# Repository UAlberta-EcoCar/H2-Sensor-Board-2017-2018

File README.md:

# H2-Sensor-(Safety)-Board
Repository for the hydrogen sensor (safety) board and associated code.

This board is responsible for shutting down the FCC system in case of a H2 leak, E-stop button push or remote-kill signal.

Preliminary documentation (to be moved to Wiki): https://drive.google.com/open?id=1S8betwiyb474213RZoNG3XHaL3DfAaQFg7lT7IdTJPk

Folder on Google Drive with other related files: https://drive.google.com/open?id=1GxiV1qDfL8EswHq86x-2SQPqP8KY5xJN

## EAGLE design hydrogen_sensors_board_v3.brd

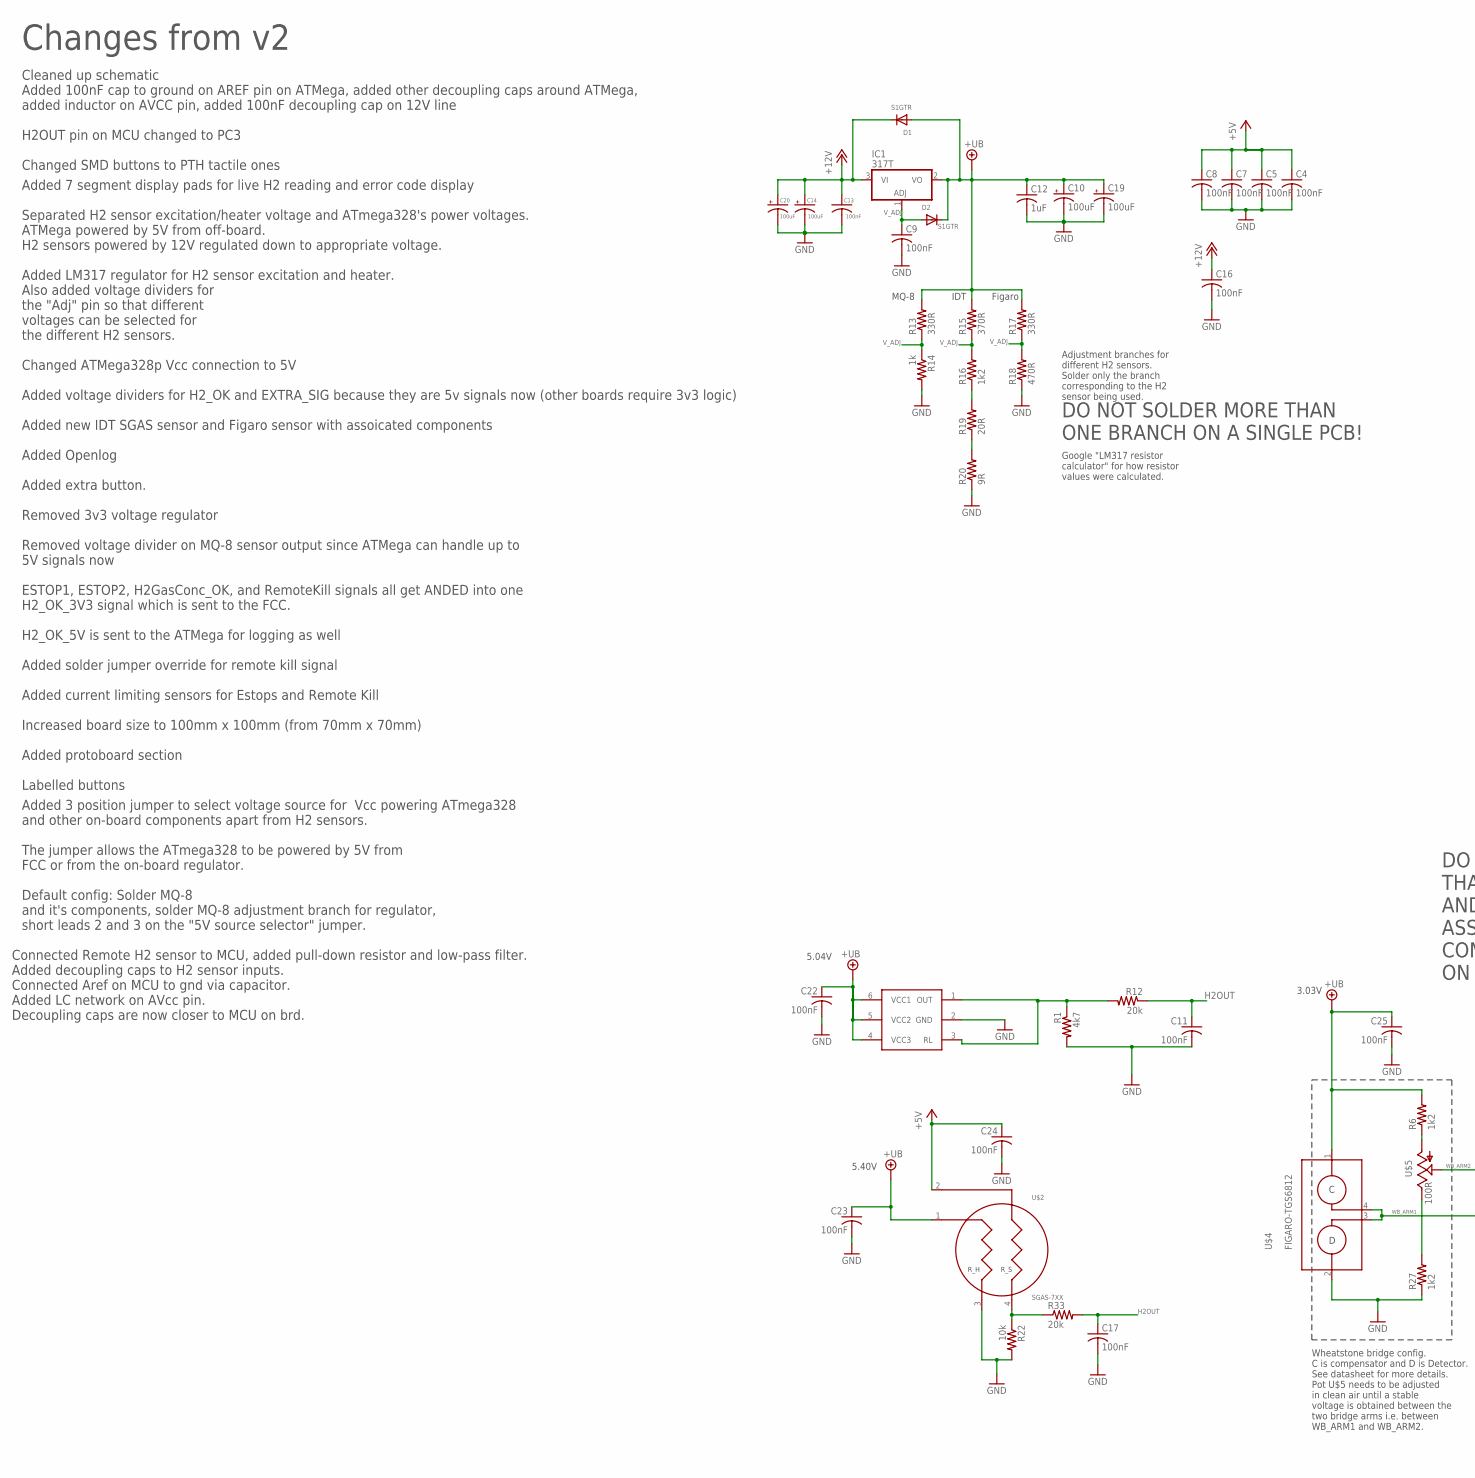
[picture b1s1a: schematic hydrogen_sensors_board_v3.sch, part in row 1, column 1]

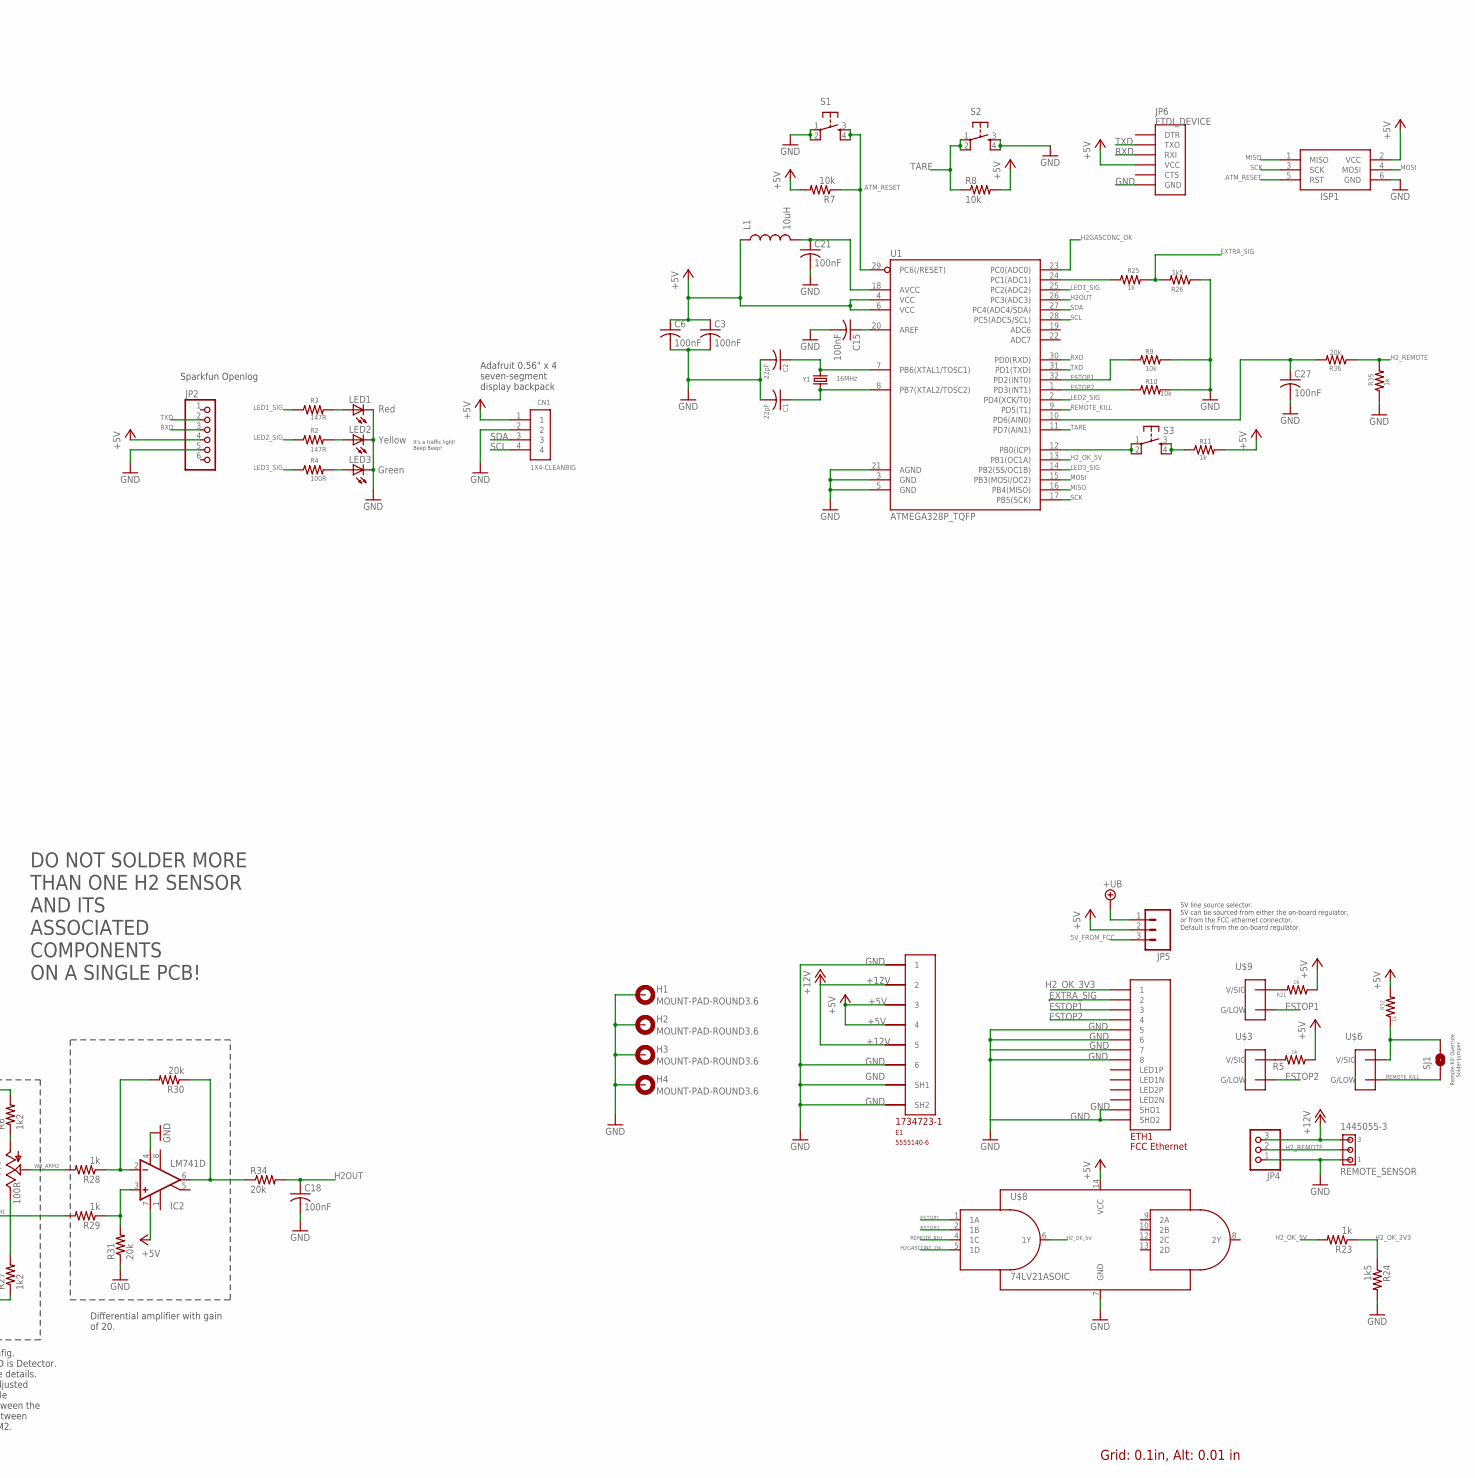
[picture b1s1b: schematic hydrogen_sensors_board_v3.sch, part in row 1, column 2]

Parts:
C1, C2: 22pF; C0603K
C3, C4, C5, C6, C7, C8, C9, C11, C13, C15, C16, C17, C18, C21, C22, C23, C24, C25, C27: 100nF; C0603
C10, C14: 100uF; B/3528-21R
C12: 1uF; C0603
C19, C20: 100uF; CPOL-RADIAL-100UF-25V
CN1: 1X4-CLEANBIG; 1X04-CLEANBIG
D1, D2: S1GTR; SMADIODE
E1: 5555140-6; 1734723-1_RJ11
ETH1: FCC Ethernet; A122645-ND
H1, H2, H3, H4: MOUNT-PAD-ROUND3.6; 3,6-PAD
IC1: 317T; TO220H
IC2: LM741D; SO08
ISP1: AVRISP-BOX
JP2: PINHD-1X6LOCK; 1X06-BIGLOCK
JP4: PINHD-1X3; 1X03
JP5: M03PTH; 1X03
JP6: FTDI_DEVICE; FTDI_DEVICE_SIDE
L1: 10uH; 0603
LED1: Red; CHIPLED_0805
LED2: Yellow; CHIPLED_0805
LED3: Green; CHIPLED_0805
R1: 4k7; 0603-RES
R2, R3: 147R; 0603-RES
R4: 100R; 0603-RES
R5, R11, R14, R21, R23, R25, R28, R29, R32, R35: 1k; 0603-RES
R6, R16, R27: 1k2; 0603-RES
R7, R8, R9, R10, R22: 10k; 0603-RES
R12, R30, R31, R33, R34, R36: 20k; 0603-RES
R13, R17: 330R; 0603-RES
R15: 370R; 0603-RES
R18: 470R; 0603-RES
R19: 20R; 0603-RES
R20: 9R; 0603-RES
R24, R26: 1k5; 0603-RES
REMOTE_SENSOR: 1445055-3
S1, S2, S3: TAC_SWITCHPTH; TACTILE-PTH
SJ1: SOLDERJUMPERNO; SJ_2S-NO
U1: ATMEGA328P_TQFP; TQFP32-08
U$1: MQ-8MQ-8; MQ-8
U$2: SGAS-7XX; TO39
U$3, U$6, U$9: TE770966; 2X1-MATE-N-LOCK
U$4: FIGARO-TGS6812; 4PTH
U$5: 100R; 3362U
U$8: 74LV21ASOIC; SOIC-14
Y1: 16MHz; HC49US

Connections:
5V_FROM_FCC: JP5.3
+5V: C3.1, C4.1, C5.1, C6.1, C7.1, C8.1, C24.1, CN1.1, E1.3, E1.4, IC2.7 (V+), ISP1.2 (VCC), JP2.4, JP5.2, JP6.P$4 (VCC), L1.1, R5.1, R7.2, R8.2, R11.2, R21.1, R32.2, U1.4 (VCC), U1.6 (VCC), U$2.2, U$8.14 (VCC)
+12V: C13.1, C14.+, C16.1, C20.1 (+), D1.C, E1.2, E1.5, IC1.3 (VI), JP4.3, REMOTE_SENSOR.3
+UB: C10.+, C12.1, C19.1 (+), C22.1, C23.1, C25.1, D1.A, D2.C, IC1.2 (VO), JP5.1, R6.2, R13.2, R15.2, R17.2, U$1.4 (VCC3), U$1.5 (VCC2), U$1.6 (VCC1), U$2.1, U$4.1
ATM_RESET: ISP1.5 (RST), R7.1, S1.3, S1.4, U1.29 (PC6(/RESET))
ESTOP1: ETH1.P$3 (3), R9.1, U1.32 (PD2(INT0)), U$8.1 (1A), U$9.CIRCUIT2 (G/LOW)
ESTOP2: ETH1.P$4 (4), R10.1, U1.1 (PD3(INT1)), U$3.CIRCUIT2 (G/LOW), U$8.2 (1B)
EXTRA_SIG: ETH1.P$2 (2), R25.2, R26.2
GND: C1.2, C2.2, C3.2, C4.2, C5.2, C6.2, C7.2, C8.2, C9.2, C10.-, C11.2, C12.2, C13.2, C14.-, C15.2, C16.2, C17.2, C18.2, C19.2 (-), C20.2 (-), C21.2, C22.2, C23.2, C24.2, C25.2, C27.2, CN1.2, E1.1, E1.6, E1.SH1, E1.SH2, ETH1.P$5 (5), ETH1.P$6 (6), ETH1.P$7 (7), ETH1.P$8 (8), ETH1.P$13 (SHD1), ETH1.P$14 (SHD2), H1.B3,6, H2.B3,6, H3.B3,6, H4.B3,6, IC2.4 (V-), ISP1.6 (GND), JP2.5, JP4.1, JP6.P$6 (GND), LED1.C, LED2.C, LED3.C, R1.2, R9.2, R10.2, R14.2, R18.1, R20.1, R22.2, R24.2, R26.1, R27.1, R31.1, R35.1, REMOTE_SENSOR.1, S1.1, S1.2, S2.3, S2.4, U1.3 (GND), U1.5 (GND), U1.21 (AGND), U$1.2 (GND), U$2.3, U$4.2, U$8.7 (GND)
H2GASCONC_OK: U1.23 (PC0(ADC0)), U$8.5 (1D)
H2OUT: C11.1, C17.1, C18.1, R12.1, R33.2, R34.2, U1.26 (PC3(ADC3))
H2_OK_3V3: ETH1.P$1 (1), R23.1, R24.1
H2_OK_5V: R23.2, U1.13 (PB1(OC1A)), U$8.6 (1Y)
H2_REMOTE: JP4.2, R35.2, R36.1, REMOTE_SENSOR.2
LED1_SIG: R3.1, U1.25 (PC2(ADC2))
LED2_SIG: R2.1, U1.2 (PD4(XCK/T0))
LED3_SIG: R4.1, U1.14 (PB2(SS/OC1B))
MISO: ISP1.1 (MISO), U1.16 (PB4(MISO))
MOSI: ISP1.4 (MOSI), U1.15 (PB3(MOSI/OC2))
unnamed: C2.1, U1.7 (PB6(XTAL1/TOSC1)), Y1.2
unnamed: R6.1, U$5.P$3 (A)
unnamed: C1.1, U1.8 (PB7(XTAL2/TOSC2)), Y1.1
unnamed: C15.1, U1.20 (AREF)
unnamed: R22.1, R33.1, U$2.4
unnamed: C27.1, R36.2, U1.10 (PD6(AIN0))
unnamed: LED1.A, R3.2
unnamed: LED2.A, R2.2
unnamed: LED3.A, R4.2
unnamed: R27.2, U$5.P$1 (E)
unnamed: R21.2, U$9.CIRCUIT1 (V/SIG)
unnamed: R25.1, U1.24 (PC1(ADC1))
unnamed: IC2.2 (-IN), R28.1, R30.2
unnamed: R16.1, R19.2
unnamed: S3.1, S3.2, U1.12 (PB0(ICP))
unnamed: R11.1, S3.3, S3.4
unnamed: R19.1, R20.2
unnamed: R1.1, R12.2, U$1.1 (OUT), U$1.3 (RL)
unnamed: IC2.6 (OUT), R30.1, R34.1
unnamed: R5.2, U$3.CIRCUIT1 (V/SIG)
unnamed: IC2.3 (+IN), R29.1, R31.2
unnamed: R32.1, SJ1.2, U$6.CIRCUIT1 (V/SIG)
unnamed: C21.1, L1.2, U1.18 (AVCC)
REMOTE_KILL: SJ1.1, U1.9 (PD5(T1)), U$6.CIRCUIT2 (G/LOW), U$8.4 (1C)
RXD: JP2.3, JP6.P$3 (RXI), U1.30 (PD0(RXD))
SCK: ISP1.3 (SCK), U1.17 (PB5(SCK))
SCL: CN1.4, U1.28 (PC5(ADC5/SCL))
SDA: CN1.3, U1.27 (PC4(ADC4/SDA))
TARE: R8.1, S2.1, S2.2, U1.11 (PD7(AIN1))
TXD: JP2.2, JP6.P$2 (TXO), U1.31 (PD1(TXD))
V_ADJ: C9.1, D2.A, IC1.1 (ADJ), R13.1, R14.1, R15.1, R16.2, R17.1, R18.2
WB_ARM1: R29.2, U$4.3, U$4.4
WB_ARM2: R28.2, U$5.P$2 (S)

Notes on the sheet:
Changes from v2
H2OUT pin on MCU changed to PC3
Changed SMD buttons to PTH tactile ones
Added 7 segment display pads for live H2 reading and error code display
Added LM317 regulator for H2 sensor excitation and heater. Also added voltage dividers for the "Adj" pin so that different voltages can be selected for the different H2 sensors.
Adafruit 0.56" x 4 seven-segment display backpack
Sparkfun Openlog
IDT
MQ-8
Figaro
Changed ATMega328p Vcc connection to 5V
Added voltage dividers for H2_OK and EXTRA_SIG because they are 5v signals now (other boards require 3v3 logic)
Added new IDT SGAS sensor and Figaro sensor with assoicated components
Added Openlog
Added extra button.
Removed 3v3 voltage regulator
Wheatstone bridge config. C is compensator and D is Detector. See datasheet for more details. Pot U$5 needs to be adjusted in clean air until a stable voltage is obtained between the two bridge arms i.e. between WB_ARM1 and WB_ARM2.
Differential amplifier with gain of 20.
3.03V
5.40V
5.04V
Adjustment branches for different H2 sensors. Solder only the branch corresponding to the H2 sensor being used.
DO NOT SOLDER MORE THAN ONE H2 SENSOR AND ITS ASSOCIATED COMPONENTS ON A SINGLE PCB!
It's a traffic light! Beep Beep!
Google "LM317 resistor calculator" for how resistor values were calculated.
Removed voltage divider on MQ-8 sensor output since ATMega can handle up to 5V signals now ESTOP1, ESTOP2, H2GasConc_OK, and RemoteKill signals all get ANDED into one H2_OK_3V3 signal which is sent to the FCC.
Grid: 0.1in, Alt: 0.01 in
Cleaned up schematic Added 100nF cap to ground on AREF pin on ATMega, added other decoupling caps around ATMega, added inductor on AVCC pin, added 100nF decoupling cap on 12V line
Increased board size to 100mm x 100mm (from 70mm x 70mm) Added protoboard section Labelled buttons
Separated H2 sensor excitation/heater voltage and ATmega328's power voltages. ATMega powered by 5V from off-board. H2 sensors powered by 12V regulated down to appropriate voltage.
DO NOT SOLDER MORE THAN ONE BRANCH ON A SINGLE PCB!
H2_OK_5V is sent to the ATMega for logging as well
Added solder jumper override for remote kill signal Added current limiting sensors for Estops and Remote Kill
Added 3 position jumper to select voltage source for Vcc powering ATmega328 and other on-board components apart from H2 sensors. The jumper allows the ATmega328 to be powered by 5V from FCC or from the on-board regulator. Default config: Solder MQ-8 and it's components, solder MQ-8 adjustment branc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
Remote Kill Override Solder Jumper
5V line source selector. 5V can be sourced from either the on-board regulator, or from the FCC ethernet connector. Default is from the on-board regulator.
Connected Remote H2 sensor to MCU, added pull-down resistor and low-pass filter. Added decoupling caps to H2 sensor inputs. Connected Aref on MCU to gnd via capacitor. Added LC network on AVcc pin. Decoupling caps are now closer to MCU on brd.

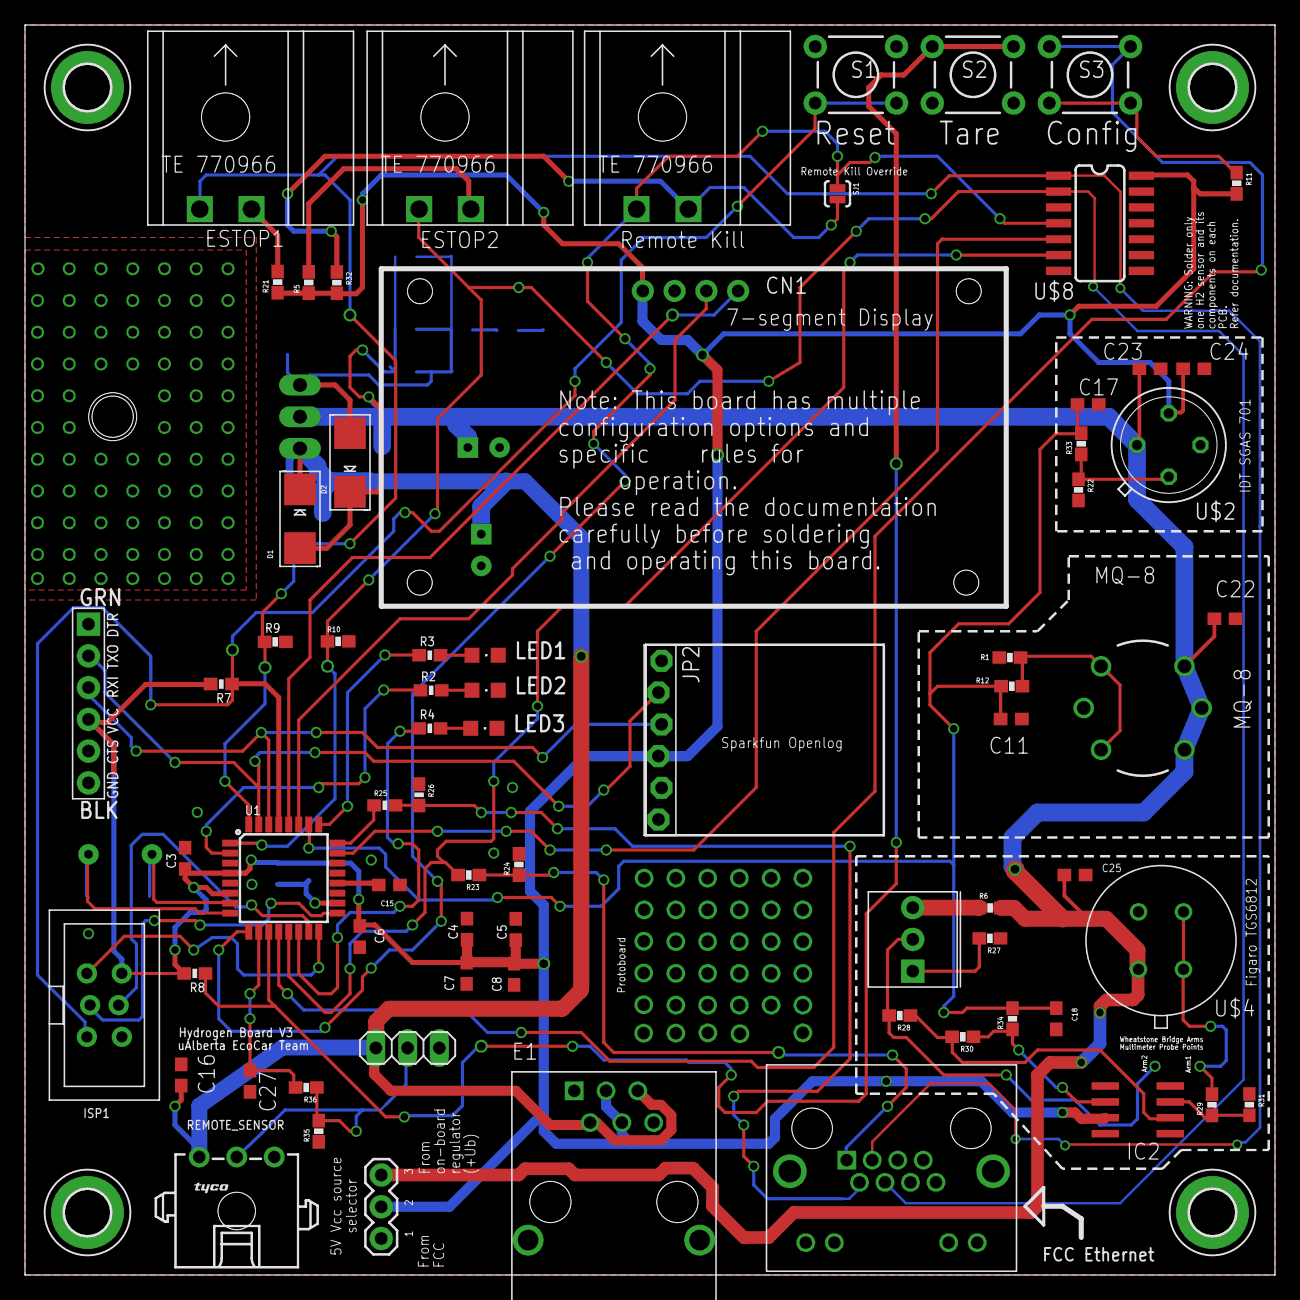
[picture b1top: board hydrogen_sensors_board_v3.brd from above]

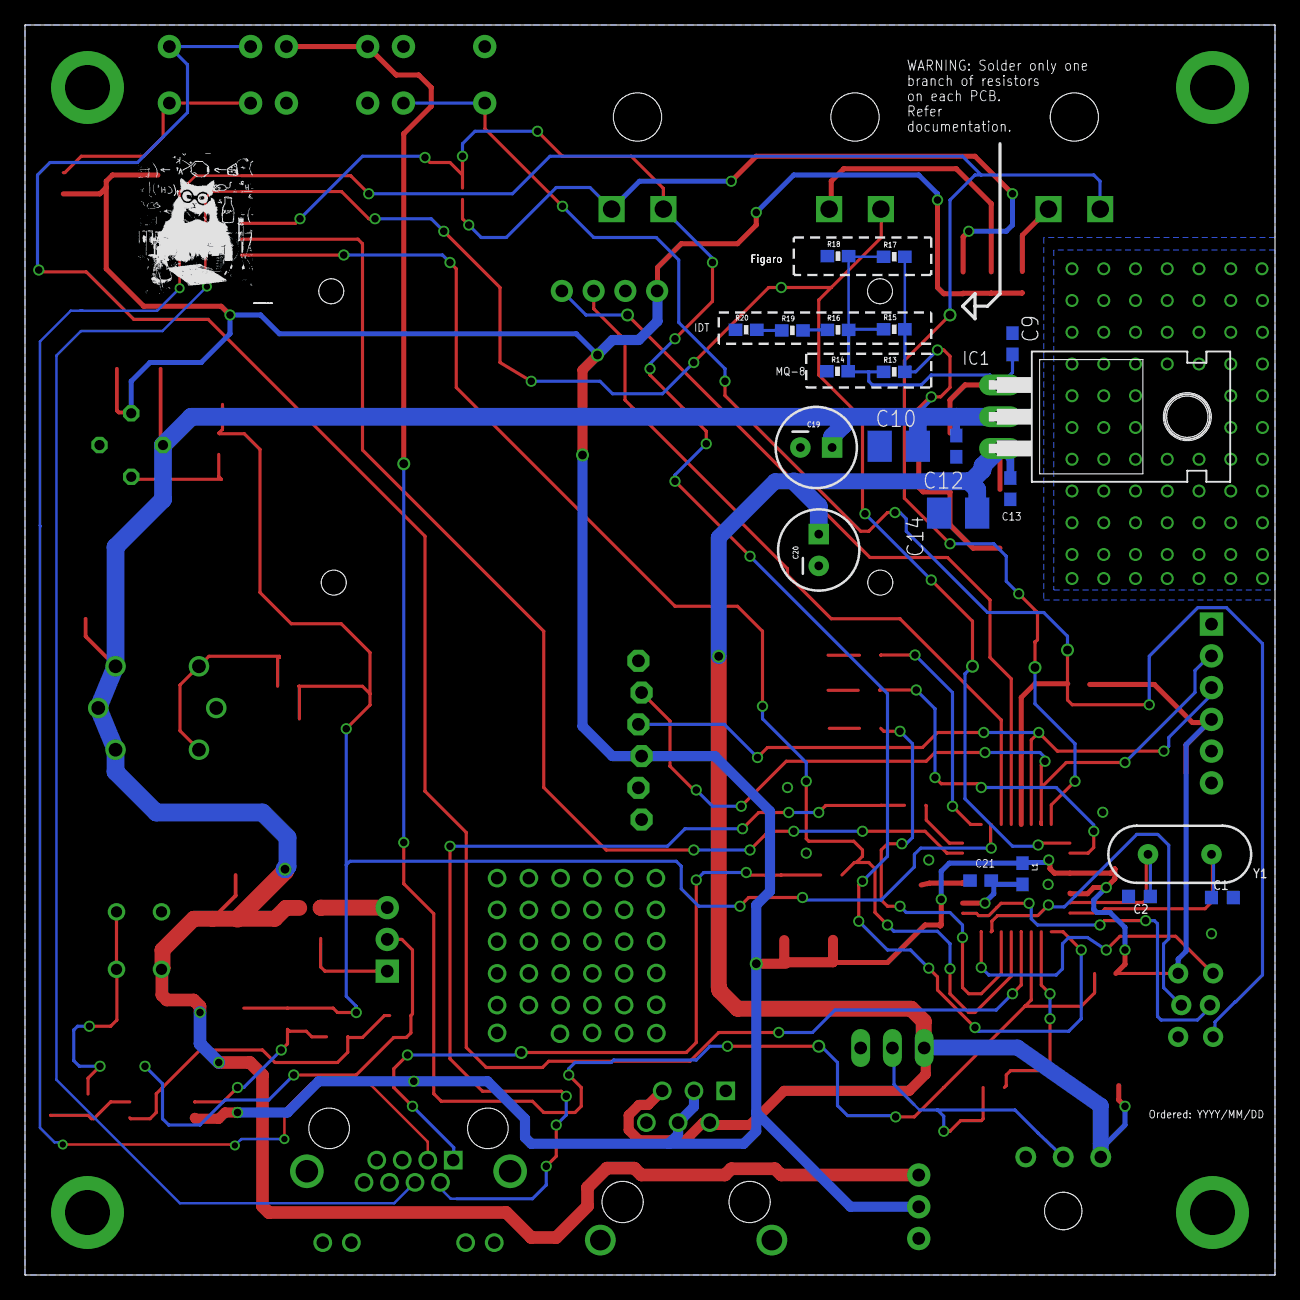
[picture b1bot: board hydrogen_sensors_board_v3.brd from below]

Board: 2 copper layers, 100.0 x 100.0 mm, 97 parts (21 on the bottom side), 51 nets.

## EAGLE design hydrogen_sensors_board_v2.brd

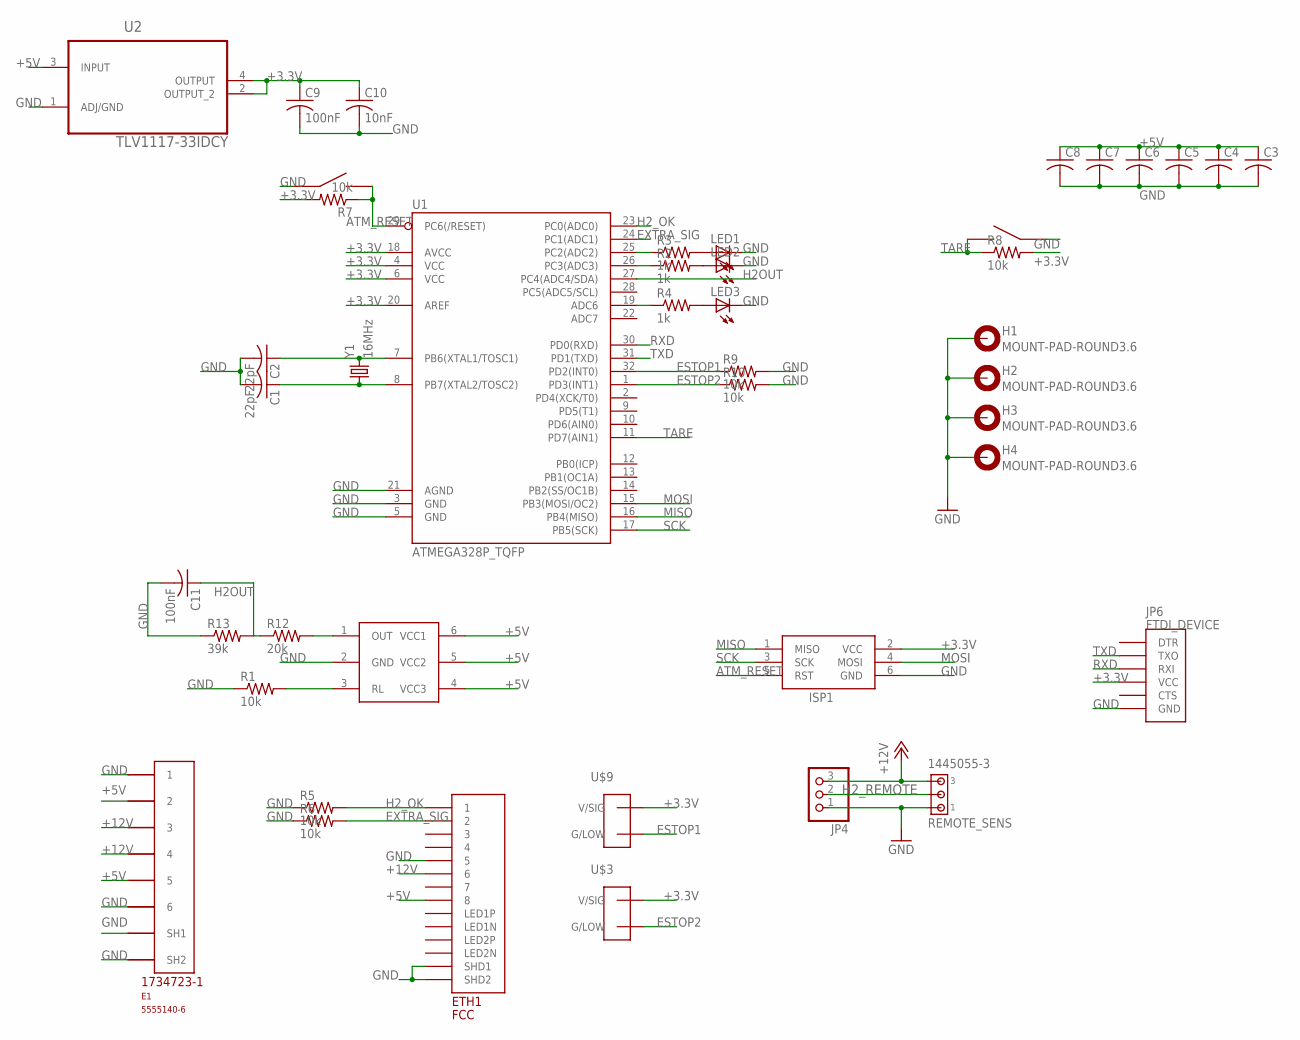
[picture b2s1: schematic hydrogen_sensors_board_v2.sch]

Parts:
C1, C2: 22pF; C0603K
C3, C4, C5, C6, C7, C8: C-USC0603; C0603
C9, C11: 100nF; C0603
C10: 10nF; C0603
E1: 5555140-6; 1734723-1_RJ11
ETH1: FCC; A122645-ND
H1, H2, H3, H4: MOUNT-PAD-ROUND3.6; 3,6-PAD
ISP1: AVRISP-BOX
JP4: PINHD-1X3; 1X03
JP6: FTDI_DEVICE; FTDI_DEVICE_SIDE
LED1, LED2, LED3: LEDCHIPLED_0805; CHIPLED_0805
R1, R5, R6, R7, R8, R9, R10: 10k; 0603-RES
R2, R3, R4: 1k; 0603-RES
R12: 20k; 0603-RES
R13: 39k; 0603-RES
REMOTE_SENS: 1445055-3
U1: ATMEGA328P_TQFP; TQFP32-08
U2: TLV1117-33IDCY; SOT230P700X180-4N
U$1: MQ-8MQ-8; MQ-8
U$2, U$10: EG4621CT-ND
U$3, U$9: TE770966; 2X1-MATE-N-LOCK
Y1: 16MHz; HC49US

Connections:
+3.3V: C9.1, C10.1, ISP1.2 (VCC), JP6.P$4 (VCC), R7.2, R8.2, U1.4 (VCC), U1.6 (VCC), U1.18 (AVCC), U1.20 (AREF), U2.2 (OUTPUT_2), U2.4 (OUTPUT), U$3.CIRCUIT1 (V/SIG), U$9.CIRCUIT1 (V/SIG)
+5V: C3.1, C4.1, C5.1, C6.1, C7.1, C8.1, E1.2, E1.5, ETH1.P$8 (8), U2.3 (INPUT), U$1.4 (VCC3), U$1.5 (VCC2), U$1.6 (VCC1)
+12V: E1.3, E1.4, ETH1.P$6 (6), JP4.3, REMOTE_SENS.3
ATM_RESET: ISP1.5 (RST), R7.1, U1.29 (PC6(/RESET)), U$10.P$3, U$10.P$4
ESTOP1: R9.1, U1.32 (PD2(INT0)), U$9.CIRCUIT2 (G/LOW)
ESTOP2: R10.1, U1.1 (PD3(INT1)), U$3.CIRCUIT2 (G/LOW)
EXTRA_SIG: ETH1.P$2 (2), R6.2, U1.24 (PC1(ADC1))
GND: C1.2, C2.2, C3.2, C4.2, C5.2, C6.2, C7.2, C8.2, C9.2, C10.2, C11.2, E1.1, E1.6, E1.SH1, E1.SH2, ETH1.P$5 (5), ETH1.P$13 (SHD1), ETH1.P$14 (SHD2), H1.B3,6, H2.B3,6, H3.B3,6, H4.B3,6, ISP1.6 (GND), JP4.1, JP6.P$6 (GND), LED1.C, LED2.C, LED3.C, R1.1, R5.1, R6.1, R9.2, R10.2, R13.1, REMOTE_SENS.1, U1.3 (GND), U1.5 (GND), U1.21 (AGND), U2.1 (ADJ/GND), U$1.2 (GND), U$2.P$1, U$2.P$2, U$10.P$1, U$10.P$2
H2OUT: C11.1, R12.1, R13.2, U1.27 (PC4(ADC4/SDA))
H2_OK: ETH1.P$1 (1), R5.2, U1.23 (PC0(ADC0))
H2_REMOTE: JP4.2, REMOTE_SENS.2
MISO: ISP1.1 (MISO), U1.16 (PB4(MISO))
MOSI: ISP1.4 (MOSI), U1.15 (PB3(MOSI/OC2))
unnamed: C2.1, U1.7 (PB6(XTAL1/TOSC1)), Y1.2
unnamed: R1.2, U$1.3 (RL)
unnamed: C1.1, U1.8 (PB7(XTAL2/TOSC2)), Y1.1
unnamed: R3.1, U1.25 (PC2(ADC2))
unnamed: R2.1, U1.26 (PC3(ADC3))
unnamed: R4.1, U1.19 (ADC6)
unnamed: LED1.A, R3.2
unnamed: LED2.A, R2.2
unnamed: LED3.A, R4.2
unnamed: R12.2, U$1.1 (OUT)
RXD: JP6.P$3 (RXI), U1.30 (PD0(RXD))
SCK: ISP1.3 (SCK), U1.17 (PB5(SCK))
TARE: R8.1, U1.11 (PD7(AIN1)), U$2.P$3, U$2.P$4
TXD: JP6.P$2 (TXO), U1.31 (PD1(TXD))

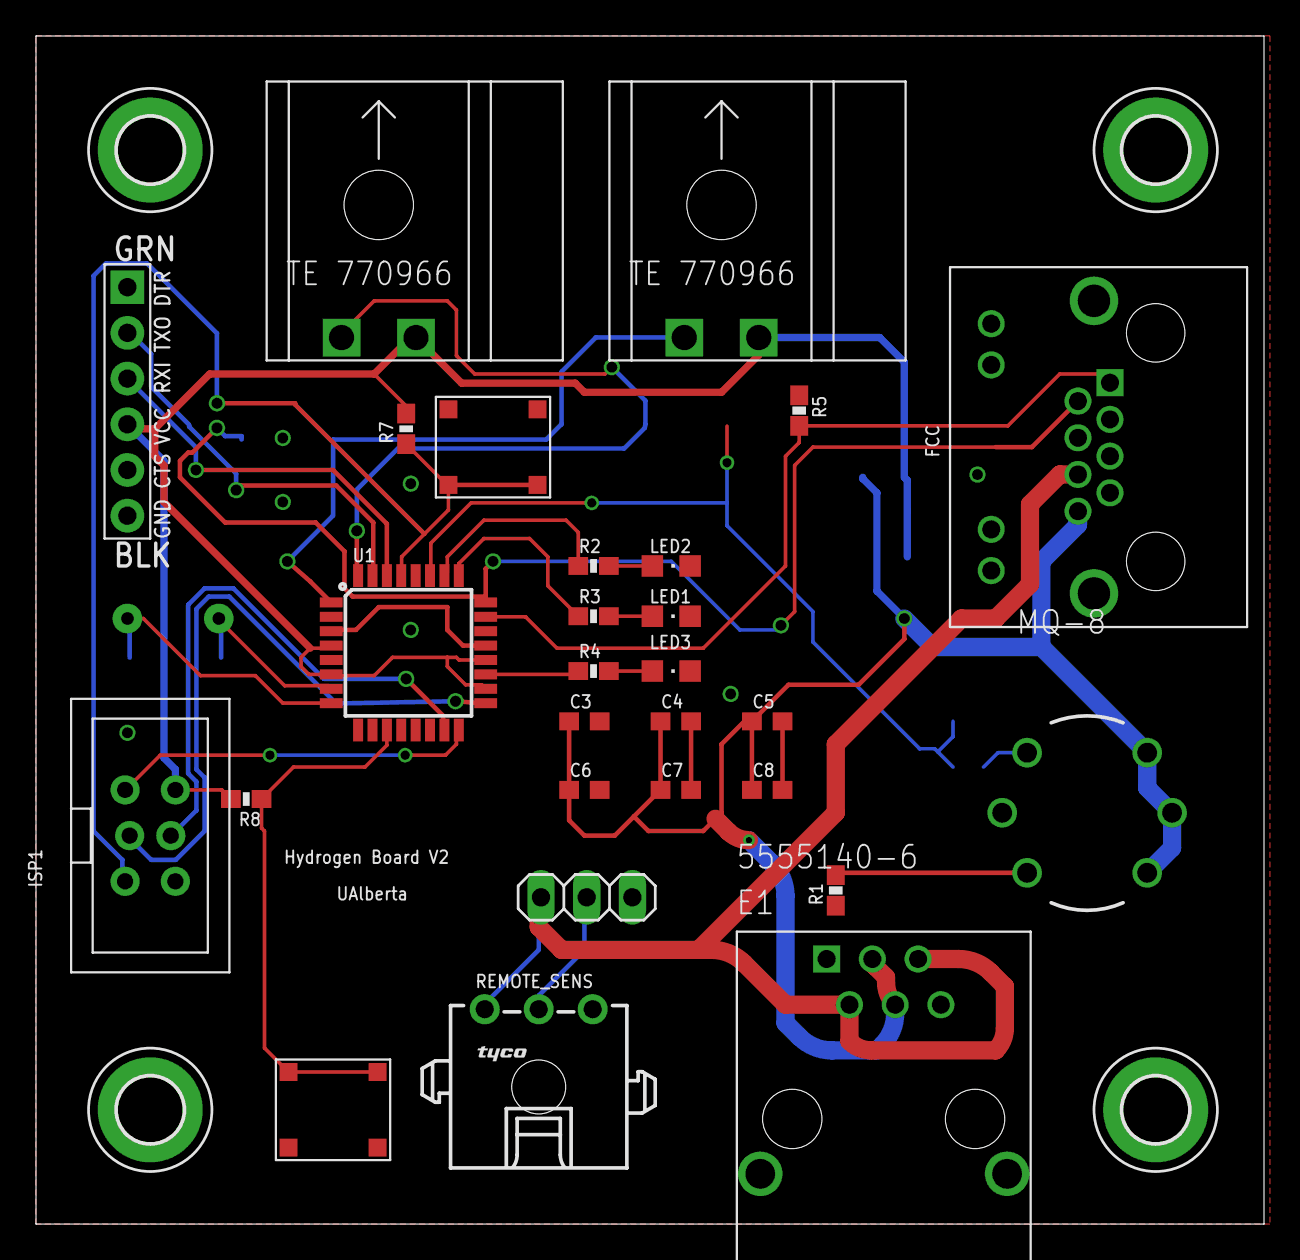
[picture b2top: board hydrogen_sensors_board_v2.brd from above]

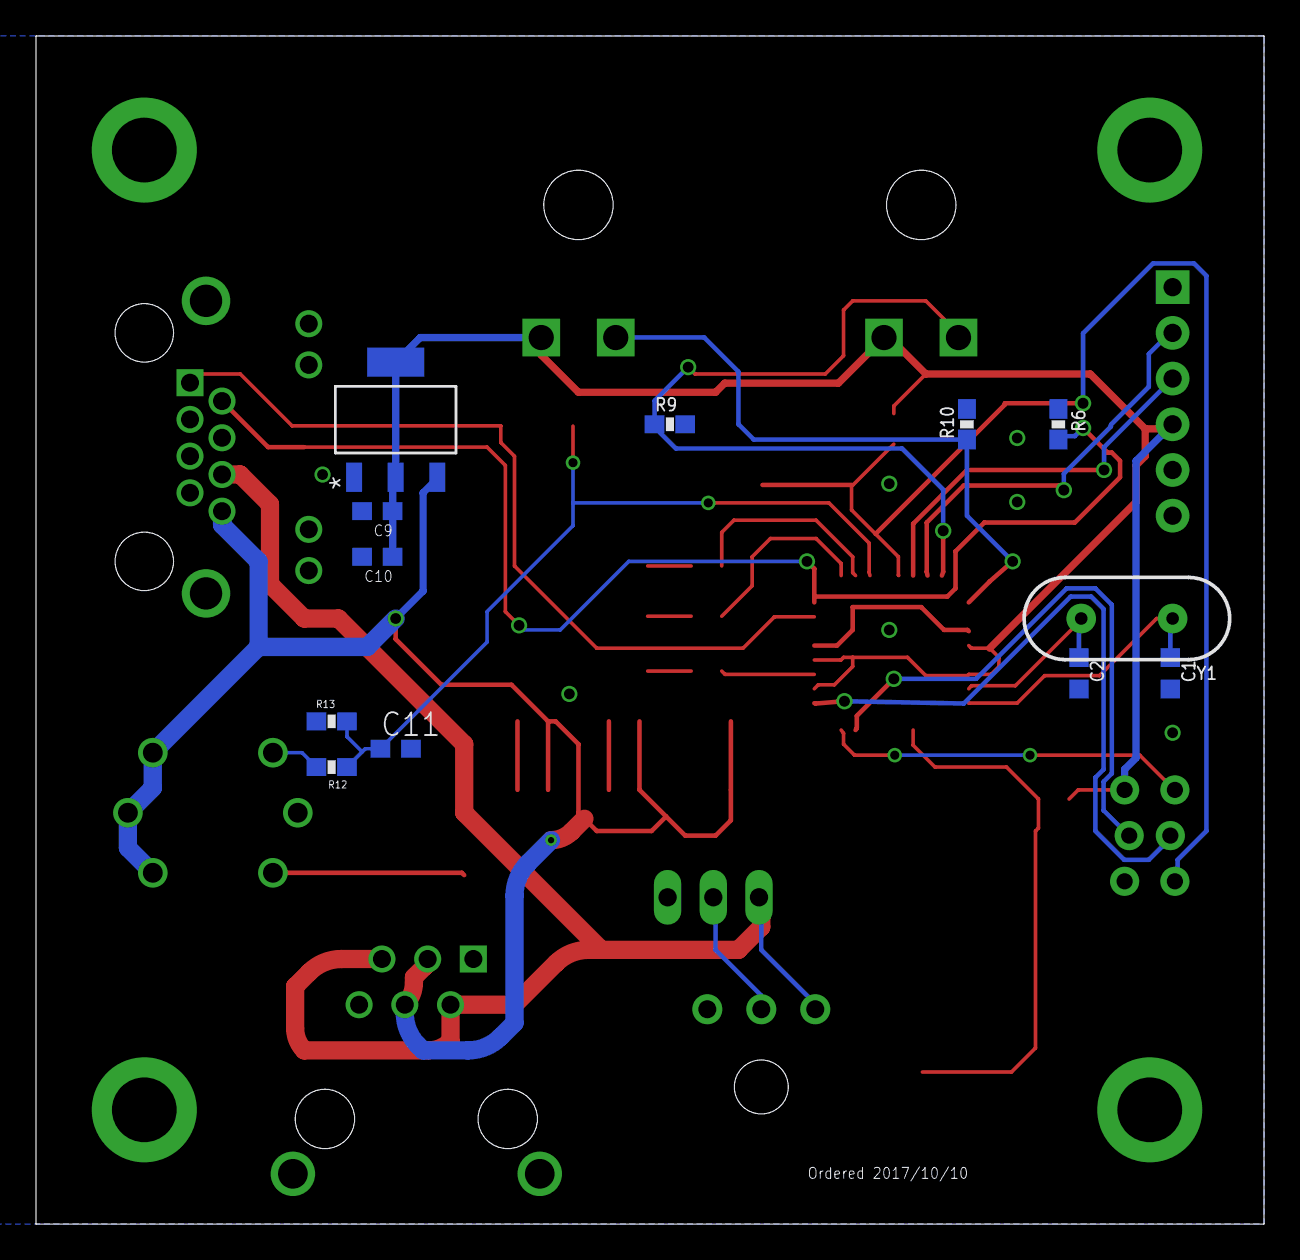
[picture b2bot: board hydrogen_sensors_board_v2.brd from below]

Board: 2 copper layers, 68.2 x 66.0 mm, 44 parts (12 on the bottom side), 27 nets.

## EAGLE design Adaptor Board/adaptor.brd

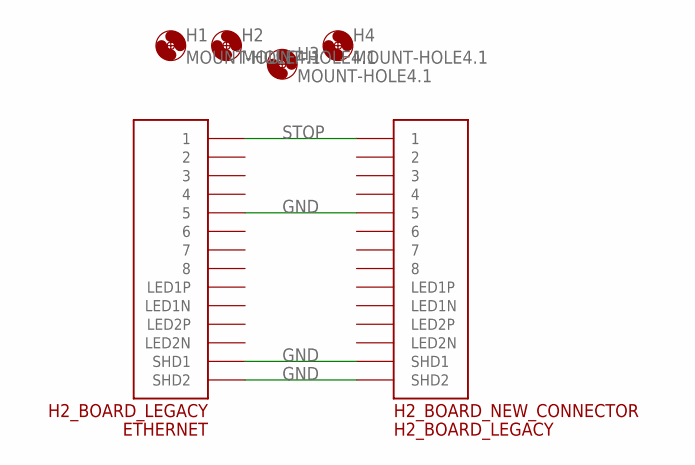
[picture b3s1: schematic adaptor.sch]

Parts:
H1, H2, H3, H4: MOUNT-HOLE4.1; 4,1
H2_BOARD_LEGACY: ETHERNET; A122645-ND
H2_BOARD_NEW_CONNECTOR: H2_BOARD_LEGACY; A122645-ND

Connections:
GND: H2_BOARD_LEGACY.P$5 (5), H2_BOARD_LEGACY.P$13 (SHD1), H2_BOARD_LEGACY.P$14 (SHD2), H2_BOARD_NEW_CONNECTOR.P$5 (5), H2_BOARD_NEW_CONNECTOR.P$13 (SHD1), H2_BOARD_NEW_CONNECTOR.P$14 (SHD2)
STOP: H2_BOARD_LEGACY.P$1 (1), H2_BOARD_NEW_CONNECTOR.P$1 (1)

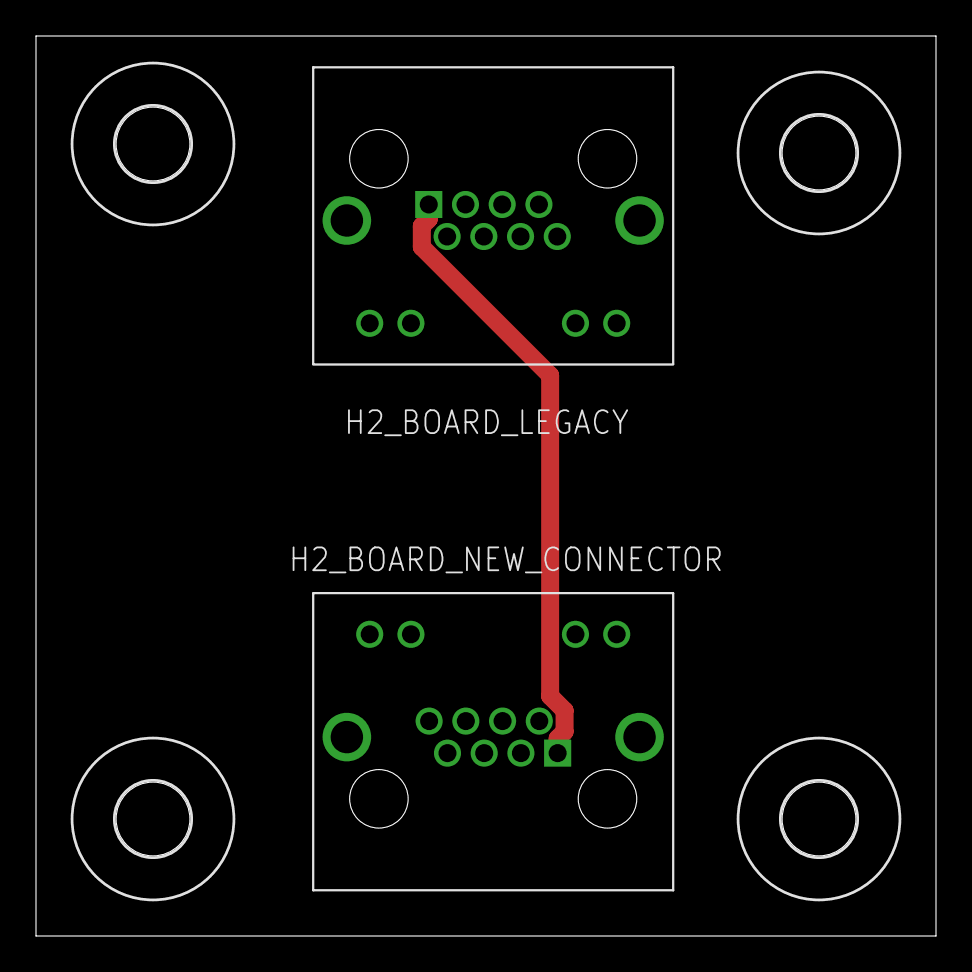
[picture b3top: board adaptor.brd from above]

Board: 2 copper layers, 50.0 x 50.0 mm, 6 parts (0 on the bottom side), 2 nets.

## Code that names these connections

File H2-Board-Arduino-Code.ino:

int H2_OK_PIN = A0; // Initialize variable for H2-board output pin
int H2_SENSOR_PIN = A4; // Initialize variable for H2-sensor output pin
int H2_LED1_PIN = A2; // Initialize variable for H2 indicator LED (LED1 on board--red)

int ESTOP1_PIN = 2; // Initialize variable for ESTOP1 pin
int ESTOP2_PIN = 3; // Initialize variable for ESTOP2 pin
int ESTOP_LED2_PIN = A3; // Initialize variable for ESTOP indicator LED (LED2 on board--blue)

int h2_sensor_value; // Initialize input variable for H2_SENSOR_PIN
int h2_sensor_cutoff = 95; // Initialize variable to store cutoff value for H2-sensor
bool estop1_value; // Initialize input variable for ESTOP1_PIN
bool estop2_value; // Initialize input variable for ESTOP2_PIN


void setup() {
  pinMode(H2_OK_PIN, OUTPUT); // Set H2_OK_PIN to output
  pinMode(H2_LED1_PIN, OUTPUT); // Set H2_LED1_PIN to output
  pinMode(ESTOP_LED2_PIN, OUTPUT); // Set ESTOP_LED2_PIN to output
  pinMode(H2_SENSOR_PIN, INPUT); // Set H2_SENSOR_PIN to input
  pinMode(ESTOP1_PIN, INPUT); // Set ESTOP1_PIN to input
  pinMode(ESTOP2_PIN, INPUT); // Set ESTOP2_PIN to input

  Serial.begin(9600); // Begin serial monitor output -- for testing and setting a value for h2_sensor_cutoff (remove later)
}

void loop() {
  h2_sensor_value = analogRead(H2_SENSOR_PIN); // Read value from H2_SENSOR_PIN and store in h2_sensor_value
  estop1_value = digitalRead(ESTOP1_PIN); // Read value from ESTOP1_PIN and store in estop1_value
  estop2_value = digitalRead(ESTOP2_PIN); // Read value from ESTOP2_PIN and store in estop2_value


  if ((estop1_value == LOW) || (estop2_value == LOW) || (h2_sensor_value >= h2_sensor_cutoff))
  {
    digitalWrite(H2_OK_PIN, LOW); // If either ESTOP is pushed or excess hydrogen is sensed, shut down system
  }
  else
  {
    digitalWrite(H2_OK_PIN, HIGH); // If everything ok, keep H2 pin set to ok
  }

  if ((estop1_value == LOW) || (estop2_value == LOW)) // If either ESTOP is pushed turn on indicator LED
  {
    digitalWrite(ESTOP_LED2_PIN, HIGH); // Turn on blue LED
  }
  else
  {
    digitalWrite(ESTOP_LED2_PIN, LOW); // If no ESTOPs are pushed keep blue LED off
  }



  if (h2_sensor_value >= h2_sensor_cutoff) // If excess hydrogen is sensed, turn on H2 indicator LED
  {
    digitalWrite(H2_LED1_PIN, HIGH); // Turn on red LED
  }
  else
  {
    digitalWrite(H2_LED1_PIN, LOW); // If no excess hydrogen, keep red LED off
  }



  Serial.println(h2_sensor_value); // Print read value from H2 sensor to serial monitor -- for testing and setting a suitable value for h2_sensor_cutoff (remove later)
  delay(500); // Delay reading to make serial monitor easier to track (remove later)

}

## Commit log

2017-10-10 Full Board Design Copied From Fuel Cell Controller Repo
2017-10-21 Small Board Clean up
2017-11-14 changed a resistor value to a standard value
2017-11-25 Revert "fixed ignore file"
    This reverts commit 2d951463a15c837006f78e97446e8d7e802643ae, reversing
    changes made to 8ab7b9f3e779fa946bec7fd04fad7310f99952af.
2017-11-25 Fix
    Merge Conflict Resolved
2017-12-05 Gerbers Generated
2017-12-05 Update Git ignore
2018-03-10 Create H2-Board-Arduino-Code
    Arduino code for H2-Sensor-Board. The lines of code used for the serial monitor to find a value for h2_sensor_cutoff should be removed after a value has been chosen -- these are marked with "(remove 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
2018-04-21 changing file extension of code to .ino
2018-04-21 adding moving average filter
2018-06-16 Added v3 of Hydrogen Sensor/Safety Board
    Cleaned up schematic
    Lots of overlapping names, text, untidy and hard to read items have been
    cleaned up.
    ATMega (MCU) pin changes
    H2OUT signal from H2 sensor(s) is on pin 26
    LED1, LED2, LED3, are on pins 25,2,14 respectively
2018-06-17 Added decoupling caps and inductor
    100nF cap moved closer to VCC pin on right side of ATmega, added
    inductor on AVCC line which then connects to 5V line. This is for more
    accurate ADC measurements as noted in datasheet. 100nF cap also added to
    12V line for decoupling.
2018-06-20 Noise filtering, R_s sensor voltage updated, updated README, brd and sch cleaned up
    Noise filtering
    Added low-pass filters to IDT SGAS and Figaro sensors.
    R_s sensor voltage updated
    IDT SGAS sensor's R_s voltage changed to 5V Vcc from 5.4V Regulator
    output (Ub). Datasheet says max permitted voltage for R_s is 5V.
    Updated README
2018-06-22 Inductor value, multimeter probe points, README
    Inductor value
    Changed inductor value on MCU AVCC pin to 10uH per datasheet
    recommendation.
    Multimeter probe points
    Added two probe points for the two arms of the Wheatstone bridge for the
    Figaro H2 sensor circuit. Will make it easy to measure voltage between
2018-06-22 Added more decoupling caps
    Added 100uF electrolytic, through-hole caps to regulator input and output. These caps are in addition to the ceramic and tantalum caps already present. Also added one more 100nF cap near the MCU.
2018-06-24 Decoupling caps, remote H2 sensor, MCU LC network, protection diodes, Figaro op-amp
    - Decoupling caps
    Added decoupling caps to H2 sensor inputs (100nF)
    - Remote H2 sensor
    Connected remote H2 sensor to MCU. Was disconnected previously. Also added pull-down resistor and low-pass filter
    - MCU LC network
    Corrected errors in LC network on AVcc pin of MCU. Capacitor was connected on Vcc side of inductor. It has now been connected to AVcc pin side of inductor as shown in the ATmega datasheet.
2018-06-25 Moved MQ-8 resistors and capacitor, updated change-log
    Moved components a bit so that they don't overlap with the MQ-8 H2 sensor.
    Updated changelog in .sch file
2018-07-01 updated rj 11 part. added signals to ethernet connector
2018-07-02 routed ESTOP Signal

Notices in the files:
parts and their libraries:
SparkFun-Connectors: Licensing: Creative Commons ShareAlike 4.0 International - https://creativecommons.org/licenses/by-sa/4.0
SparkFun: Licensing: CC v3.0 Share-Alike You are welcome to use this library for commercial purposes.
